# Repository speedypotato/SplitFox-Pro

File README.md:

# SplitFox-Pro
Split-style Pro Leverless Controller

#### This work is licensed under a Creative Commons Attribution-NonCommercial-ShareAlike 4.0 International License.

### Prototype Run For Sale @ https://www.speedylabs.us/product/splitfox-pro-split-fighting-box-pro/ 

## What's the SplitFox Pro?
Speedy Labs introduces the SplitFox Pro - Split Fighting Box (Pro)!  This is a split layout leverless controller with 18 action buttons, 6 aux buttons, and a tournament lockout switch running on GP2040-CE.

### Design
When designing this, I had a few main goals in mind:
1. Split Layout
2. Embeddable PS Auth Dongle (non-protruding)
3. Standard or Mixbox support
4. USB C Daughterboard

Technically this would have been the LightFox Pro, but since I'm using choc v2 here due to the rumored discontinuation of Keychron LP Opticals it would feel wrong to call it that.  Hence SplitFox Pro.  The layout begins with the standard 12 button leverless layout.  I then took the 4 movement buttons and shifted them out one button space, creating the basic split layout.  I then added a button to each side of each thumb, as typical of many 16 button leverless layouts (except these only have one center thumb button, where SplitFox Pro has two).  Similarly, I added an extra button above the punch row as it's very typical to see one here in addition to a left hand pinky button because I believe that all fingers should be able to press a button at a moment's notice.

Some smaller goals, many carried over from the LightFox:
- Maintain acrylic top for artwork
- Aux buttons on both sides of controller for ease of use/preference
- OLED Display
- Mid-frame construction

### BOM
- PCBs
  - 1x SplitFox
  - 1x wasd or wasd-m
  - 1x usb-breakout
  - 1x usb-ext (optional)
- 1x OLED ZJY096-2864KSWEG41X
- Acrylics (2.5mm thickness)
  - 1x splitfox-bottom
  - 1x splitfox-top or splitfox-top-m
- CNC Aluminum (or 3D print if going for a cheaper build)
  - 1x splitfox-body
  - 1x splitfox-wasd-1_2mm or splitfox-wasd-m-1_2mm (both 1.2mm thick)
- 2x EVA Foam Feet splitfox-foot-2mm (or silicone, but it was too expensive for a small run for me)
- 23x m3x6 ultra low profile screws
- 2x m3 nut
- 18x shadow hunting switches (or any choc v2 switch)
- Keycaps
  - 4x 28.5mm
  - 14x 22.5 or 10x 22.5 + WASD (must be low profile mx stem compatible!!)
- Double sided mounting tape (Scotch 314H-MED is a good thickness for the oled in my tests)
- 2x ZH 7 Pin 10cm double headed wire (make sure you don't get the twisted cable version!! correct version e.g. https://ae01.alicdn.com/kf/S88d212727fc34138a45582e0e0a23c315.jpg)
- 3D prints
  - 1x usb-ext-bot
  - 1x usb-ext-top
  - 1x 93657A501_Nylon Unthreaded Spacer

Optionals, but things I would include normally:
- 1x 2mm hex wrench
- 1x 2m usb c cable
- 1x velcro cable tie
- 1x zipper case
- 1x shipping box
- 1x honson F5

### Basic Assembly Instructions
0. Flash SplitFox pcb
1. Plug in OLED and adhere with double sided mounting tape.
2. Plug both ZH cable into SplitFox pcb
3. Screw in SplitFox pcb into splitfox-body
4. Plug WASD ZH cable into wasd pcb
5. Screw wasd pcb into splitfox-body
6. Put splitfox-wasd-1_2mm into topside of splitfox-body, using 93657A501_Nylon Unthreaded Spacer, 1x m3x6, and 1x m3 nut to secure and sandwich together.
7. Insert shadow hunting switches.  Support sockets from backside when inserting to avoid damage.
8. Plug USB ZH cable into usb-breakout pcb
9. Screw in usb-breakout pcb into splitfox-body
10. Apply 2x splitfox-foot-2mm to splitfox-bottom
11. Screw in splitfox-bottom to splitfox-body
12. Add artwork cutout if desired
13. Screw in splitfox-top to splitfox-body

### Video Guides
SplitFox Pro Assembly & Mixbox Setup: https://youtu.be/-rr3WSn5i6s  
SplitFox Pro LED Setup (Beta): https://youtu.be/0wB09UQQ0kg

Done!  Be sure to post your builds on Discord @ https://discord.gg/MmuKd73XbY or Twitter/X and tag me @SpeedyPotato_

### Known Issues
v1.1 SplitFox fixes below issue by changing back to the crystal setup I used to use.  Could also be just a bad batch from v1 as I used a different PCBa for v1.1 too.

With v1, testing has gone fairly smoothly aside from one weird issue, where plugging in an auth dongle causes the controller to freeze/reboot.  If you leave the dongle plugged in all the time, this isn't an issue, but I hope to root cause it someday.  It might be the RP2040 crystal setup or the XC6206 being too weak, but both are also fairly tested in other controllers that don't have issues.  RP2040 crystal setup is new to me but is recommended in RP2040's hardware design guide.  XC6206 is used in production LightFox controllers and those have no issues hotplugging auth devices.

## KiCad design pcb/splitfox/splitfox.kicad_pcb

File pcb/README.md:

# PCB

This is where the PCB source file(s) live

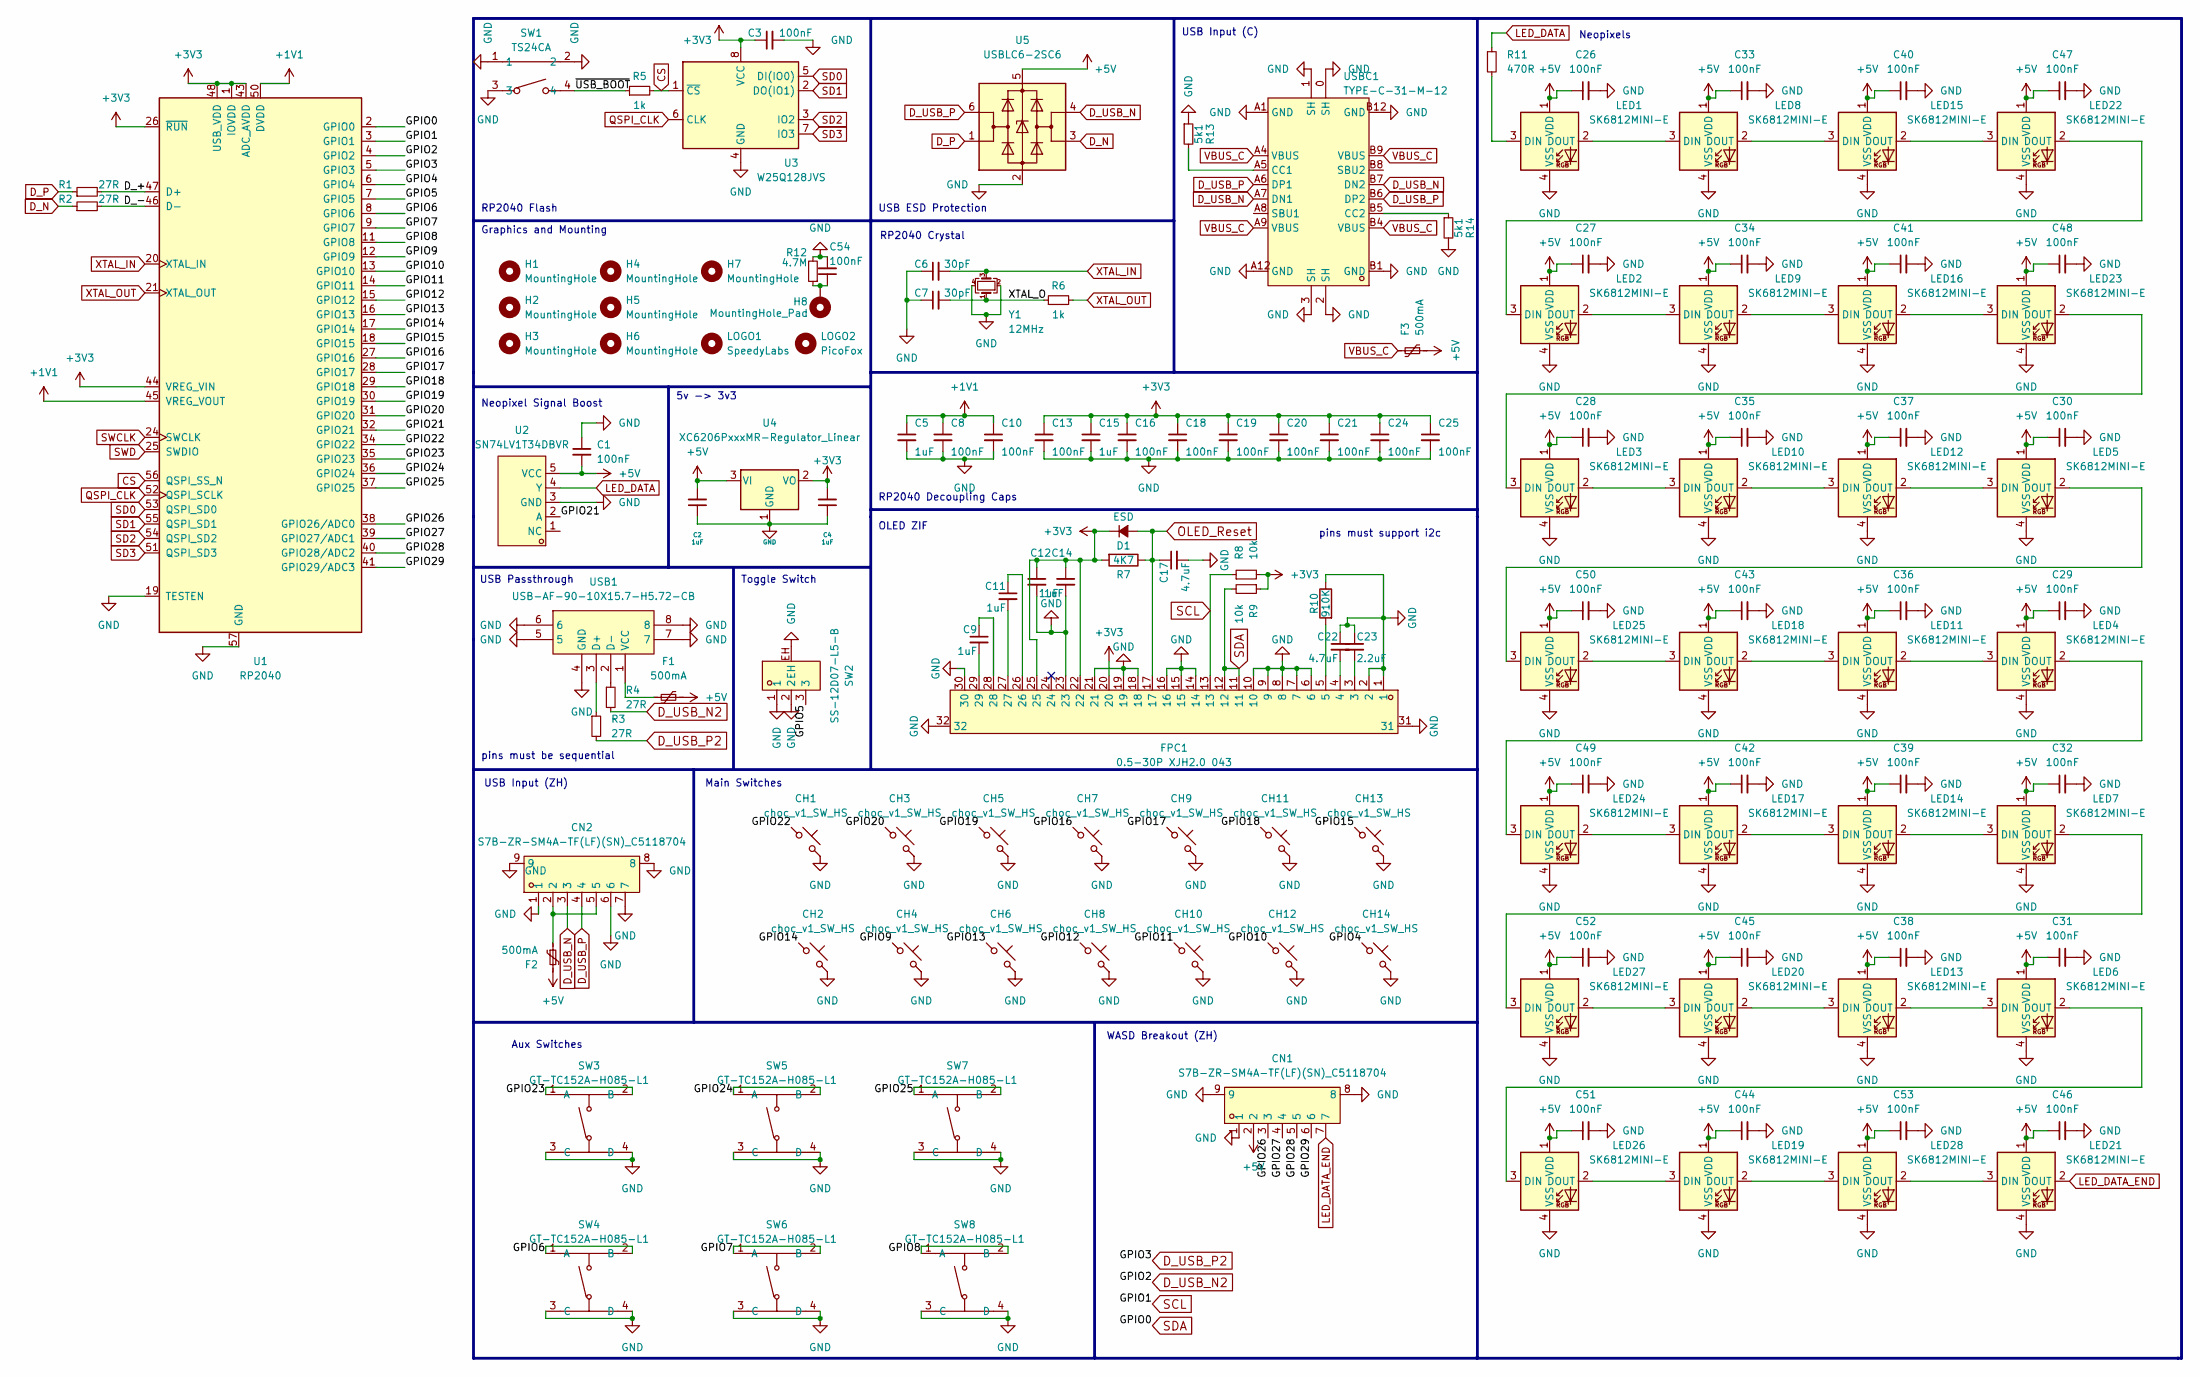
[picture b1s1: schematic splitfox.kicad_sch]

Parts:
C1, C3, C8, C10, C13, C16, C18, C19, C20, C21, C24, C25, C26, C27, C28, C29, C30, C31, C32, C33, C34, C35, C36, C37, C38, C39, C40, C41, C42, C43, C44, C45, C46, C47, C48, C49, C50, C51, C52, C53, C54: 100nF; C_0402_1005Metric; LCSC C1525
C2, C4, C5, C9, C11, C12, C14, C15: 1uF; C_0402_1005Metric; LCSC C52923
C6, C7: 30pF; C_0402_1005Metric; LCSC C1570
C17, C22: 4.7uF; C_0402_1005Metric; LCSC C466620
C23: 2.2uF; C_0402_1005Metric; LCSC C2976056
CH1, CH2, CH3, CH4, CH5, CH6, CH7, CH8, CH9, CH10, CH11, CH12, CH13, CH14: choc_v1_SW_HS; SW_choc_v2_HS_CPG135001S30_1u; LCSC C5333465
CN1, CN2: S7B-ZR-SM4A-TF(LF)(SN)_C5118704; CONN-SMD_S7B-ZR-SM4A-TF-LF-SN; LCSC Part C5118704
D1: ESD; D_SOD-123; LCSC C81598
F1, F2, F3: 500mA; Fuse_1206_3216Metric; LCSC C720075
FPC1: 0.5-30P XJH2.0 043; FPC-SMD_30P-P0.50_0.5-30P-XJH2.0-043; LCSC Part C5373440
H1, H2, H3, H4, H5, H6, H7: MountingHole; MountingHole_3mm
H8: MountingHole_Pad; MountingHole_3mm_Pad
LED1, LED2, LED3, LED4, LED5, LED6, LED7, LED8, LED9, LED10, LED11, LED12, LED13, LED14, LED15, LED16, LED17, LED18, LED19, LED20, LED21, LED22, LED23, LED24, LED25, LED26, LED27, LED28: SK6812MINI-E; LED_6028R; LCSC C5149201
LOGO1: SpeedyLabs; logo
LOGO2: PicoFox; picofox_small
R1, R2, R3, R4: 27R; R_0402_1005Metric; LCSC C137890
R5, R6: 1k; R_0402_1005Metric; LCSC C11702
R7: 4K7; R_0402_1005Metric; LCSC C25900
R8, R9: 10k; R_0402_1005Metric; LCSC C25744
R10: 910K; R_0402_1005Metric; LCSC C25800
R11: 470R; R_0402_1005Metric; LCSC C25117
R12: 4.7M; R_0402_1005Metric; LCSC C474132
R13, R14: 5k1; R_0402_1005Metric; LCSC C25905
SW1: TS24CA; SW-SMD_TS24CA; LCSC Part C393942
SW2: SS-12D07-L5-B; SW-TH_SS-12D07-X-X; LCSC Part C480345
SW3, SW4, SW5, SW6, SW7, SW8: GT-TC152A-H085-L1; SW-TH_4P-L12.0-W12.0-P5.00-LS12.5; LCSC Part C2843937
U1: RP2040; RP2040-QFN-56; LCSC C2040
U2: SN74LV1T34DBVR; SOT-23-5_L2.9-W1.6-P0.95-LS2.8-BR; LCSC Part C100024
U3: W25Q128JVS; SOIC-8_5.23x5.23mm_P1.27mm; LCSC C131025
U4: XC6206PxxxMR-Regulator_Linear; SOT-23; LCSC C5446
U5: USBLC6-2SC6; SOT-23-6; LCSC C2827654
USB1: USB-AF-90-10X15.7-H5.72-CB; USB-A-SMD_C41014; LCSC Part C41014
USBC1: TYPE-C-31-M-12; USB-C_SMD-TYPE-C-31-M-12; LCSC Part C165948
Y1: 12MHz; Crystal_SMD_3225-4Pin_3.2x2.5mm; LCSC C9002

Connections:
+1V1: C5.1, C8.1, C10.1, U1.23 (DVDD), U1.45 (VREG_VOUT), U1.50 (DVDD)
+3V3: C3.1, C4.2, C12.1, C13.1, C14.1, C15.1, C16.1, C18.1, C19.1, C20.1, C21.1, C24.1, C25.1, D1.1 (K), FPC1.20, FPC1.22, FPC1.25, R7.2, R8.2, R9.1, U1.1 (IOVDD), U1.10 (IOVDD), U1.22 (IOVDD), U1.26 (~RUN), U1.33 (IOVDD), U1.42 (IOVDD), U1.43 (ADC_AVDD), U1.44 (VREG_VIN), U1.48 (USB_VDD), U1.49 (IOVDD), U3.8 (VCC), U4.2 (VO)
+5V: C1.2, C2.2, C26.1, C27.1, C28.1, C29.1, C30.1, C31.1, C32.1, C33.1, C34.1, C35.1, C36.1, C37.1, C38.1, C39.1, C40.1, C41.1, C42.1, C43.1, C44.1, C45.1, C46.1, C47.1, C48.1, C49.1, C50.1, C51.1, C52.1, C53.1, CN1.2, F1.1, F2.2, F3.1, LED1.1 (VDD), LED2.1 (VDD), LED3.1 (VDD), LED4.1 (VDD), LED5.1 (VDD), LED6.1 (VDD), LED7.1 (VDD), LED8.1 (VDD), LED9.1 (VDD), LED10.1 (VDD), LED11.1 (VDD), LED12.1 (VDD), LED13.1 (VDD), LED14.1 (VDD), LED15.1 (VDD), LED16.1 (VDD), LED17.1 (VDD), LED18.1 (VDD), LED19.1 (VDD), LED20.1 (VDD), LED21.1 (VDD), LED22.1 (VDD), LED23.1 (VDD), LED24.1 (VDD), LED25.1 (VDD), LED26.1 (VDD), LED27.1 (VDD), LED28.1 (VDD), U2.5 (VCC), U4.3 (VI), U5.5 (VBUS)
/D_+: R1.2, U1.47 (D+)
/D_-: R2.2, U1.46 (D-)
/GPIO4: CH14.1, U1.6 (GPIO4)
/GPIO5: SW2.3, U1.7 (GPIO5)
/GPIO6: SW4.1 (A), SW4.2 (B), U1.8 (GPIO6)
/GPIO7: SW6.1 (A), SW6.2 (B), U1.9 (GPIO7)
/GPIO8: SW8.1 (A), SW8.2 (B), U1.11 (GPIO8)
/GPIO9: CH4.1, U1.12 (GPIO9)
/GPIO10: CH12.1, U1.13 (GPIO10)
/GPIO11: CH10.1, U1.14 (GPIO11)
/GPIO12: CH8.1, U1.15 (GPIO12)
/GPIO13: CH6.1, U1.16 (GPIO13)
/GPIO14: CH2.1, U1.17 (GPIO14)
/GPIO15: CH13.1, U1.18 (GPIO15)
/GPIO16: CH7.1, U1.27 (GPIO16)
/GPIO17: CH9.1, U1.28 (GPIO17)
/GPIO18: CH11.1, U1.29 (GPIO18)
/GPIO19: CH5.1, U1.30 (GPIO19)
/GPIO20: CH3.1, U1.31 (GPIO20)
/GPIO21: U1.32 (GPIO21), U2.2 (A)
/GPIO22: CH1.1, U1.34 (GPIO22)
/GPIO23: SW3.1 (A), SW3.2 (B), U1.35 (GPIO23)
/GPIO24: SW5.1 (A), SW5.2 (B), U1.36 (GPIO24)
/GPIO25: SW7.1 (A), SW7.2 (B), U1.37 (GPIO25)
/GPIO26: CN1.3, U1.38 (GPIO26/ADC0)
/GPIO27: CN1.4, U1.39 (GPIO27/ADC1)
/GPIO28: CN1.5, U1.40 (GPIO28/ADC2)
/GPIO29: CN1.6, U1.41 (GPIO29/ADC3)
/XTAL_O: C7.2, R6.1, Y1.1
/~USB_BOOT: R5.1, SW1.4
CS: R5.2, U1.56 (QSPI_SS_N), U3.1 (~CS)
D_N: R2.1, U5.3 (I/O2)
D_P: R1.1, U5.1 (I/O1)
D_USB_N: CN2.3, U5.4 (I/O2), USBC1.A7 (DN1), USBC1.B7 (DN2)
D_USB_N2: R4.2, U1.4 (GPIO2)
D_USB_P: CN2.4, U5.6 (I/O1), USBC1.A6 (DP1), USBC1.B6 (DP2)
D_USB_P2: R3.2, U1.5 (GPIO3)
GND: C1.1, C2.1, C3.2, C4.1, C5.2, C6.1, C7.1, C8.2, C10.2, C12.2, C13.2, C14.2, C15.2, C16.2, C17.2, C18.2, C19.2, C20.2, C21.2, C22.1, C23.1, C24.2, C25.2, C26.2, C27.2, C28.2, C29.2, C30.2, C31.2, C32.2, C33.2, C34.2, C35.2, C36.2, C37.2, C38.2, C39.2, C40.2, C41.2, C42.2, C43.2, C44.2, C45.2, C46.2, C47.2, C48.2, C49.2, C50.2, C51.2, C52.2, C53.2, C54.2, CH1.2, CH2.2, CH3.2, CH4.2, CH5.2, CH6.2, CH7.2, CH8.2, CH9.2, CH10.2, CH11.2, CH12.2, CH13.2, CH14.2, CN1.1, CN1.8, CN1.9, CN2.1, CN2.6, CN2.7, CN2.8, CN2.9, FPC1.1, FPC1.2, FPC1.6, FPC1.7, FPC1.8, FPC1.9, FPC1.10, FPC1.14, FPC1.15, FPC1.16, FPC1.18, FPC1.19, FPC1.21, FPC1.23, FPC1.30, FPC1.31, FPC1.32, LED1.4 (VSS), LED2.4 (VSS), LED3.4 (VSS), LED4.4 (VSS), LED5.4 (VSS), LED6.4 (VSS), LED7.4 (VSS), LED8.4 (VSS), LED9.4 (VSS), LED10.4 (VSS), LED11.4 (VSS), LED12.4 (VSS), LED13.4 (VSS), LED14.4 (VSS), LED15.4 (VSS), LED16.4 (VSS), LED17.4 (VSS), LED18.4 (VSS), LED19.4 (VSS), LED20.4 (VSS), LED21.4 (VSS), LED22.4 (VSS), LED23.4 (VSS), LED24.4 (VSS), LED25.4 (VSS), LED26.4 (VSS), LED27.4 (VSS), LED28.4 (VSS), R10.1, R12.2, R13.1, R14.2, SW1.1, SW1.2, SW1.3, SW2.1, SW2.2, SW2.EH, SW3.3 (C), SW3.4 (D), SW4.3 (C), SW4.4 (D), SW5.3 (C), SW5.4 (D), SW6.3 (C), SW6.4 (D), SW7.3 (C), SW7.4 (D), SW8.3 (C), SW8.4 (D), U1.19 (TESTEN), U1.57 (GND), U2.3 (GND), U3.4 (GND), U4.1 (GND), U5.2 (GND), USB1.4 (GND), USB1.5, USB1.6, USB1.7, USB1.8, USBC1.0 (SH), USBC1.1 (SH), USBC1.2 (SH), USBC1.3 (SH), USBC1.A1 (GND), USBC1.A12 (GND), USBC1.B1 (GND), USBC1.B12 (GND), Y1.2, Y1.4
LED_DATA: R11.1, U2.4 (Y)
LED_DATA_END: CN1.7, LED21.2 (DOUT)
unnamed: C9.1, FPC1.28
unnamed: C9.2, FPC1.29
unnamed: C11.1, FPC1.26
unnamed: C11.2, FPC1.27
unnamed: C22.2, FPC1.4
unnamed: C23.2, FPC1.3
unnamed: C54.1, H8.1, R12.1
unnamed: CN2.2, CN2.5, F2.1
unnamed: FPC1.5, R10.2
unnamed: LED1.3 (DIN), R11.2
unnamed: LED1.2 (DOUT), LED8.3 (DIN)
unnamed: LED2.3 (DIN), LED22.2 (DOUT)
unnamed: LED2.2 (DOUT), LED9.3 (DIN)
unnamed: LED3.2 (DOUT), LED10.3 (DIN)
unnamed: LED10.2 (DOUT), LED12.3 (DIN)
unnamed: LED11.3 (DIN), LED18.2 (DOUT)
unnamed: LED4.3 (DIN), LED11.2 (DOUT)
unnamed: LED5.3 (DIN), LED12.2 (DOUT)
unnamed: LED13.3 (DIN), LED20.2 (DOUT)
unnamed: LED6.3 (DIN), LED13.2 (DOUT)
unnamed: LED14.3 (DIN), LED17.2 (DOUT)
unnamed: LED7.3 (DIN), LED14.2 (DOUT)
unnamed: LED8.2 (DOUT), LED15.3 (DIN)
unnamed: LED15.2 (DOUT), LED22.3 (DIN)
unnamed: LED9.2 (DOUT), LED16.3 (DIN)
unnamed: LED16.2 (DOUT), LED23.3 (DIN)
unnamed: LED17.3 (DIN), LED24.2 (DOUT)
unnamed: LED18.3 (DIN), LED25.2 (DOUT)
unnamed: LED19.3 (DIN), LED26.2 (DOUT)
unnamed: LED19.2 (DOUT), LED28.3 (DIN)
unnamed: LED20.3 (DIN), LED27.2 (DOUT)
unnamed: LED21.3 (DIN), LED28.2 (DOUT)
unnamed: LED3.3 (DIN), LED23.2 (DOUT)
unnamed: LED4.2 (DOUT), LED24.3 (DIN)
unnamed: LED5.2 (DOUT), LED25.3 (DIN)
unnamed: LED6.2 (DOUT), LED26.3 (DIN)
unnamed: LED7.2 (DOUT), LED27.3 (DIN)
unnamed: R3.1, USB1.3 (D+)
unnamed: R4.1, USB1.2 (D-)
unnamed: F1.2, USB1.1 (VCC)
unnamed: R13.2, USBC1.A5 (CC1)
unnamed: R14.1, USBC1.B5 (CC2)
OLED_Reset: C17.1, D1.2 (A), FPC1.17, R7.1
QSPI_CLK: U1.52 (QSPI_SCLK), U3.6 (CLK)
SCL: FPC1.13, R8.1, U1.3 (GPIO1)
SD0: U1.53 (QSPI_SD0), U3.5 (DI(IO0))
SD1: U1.55 (QSPI_SD1), U3.2 (DO(IO1))
SD2: U1.54 (QSPI_SD2), U3.3 (IO2)
SD3: U1.51 (QSPI_SD3), U3.7 (IO3)
SDA: FPC1.11, FPC1.12, R9.2, U1.2 (GPIO0)
SWCLK: U1.24 (SWCLK)
SWD: U1.25 (SWDIO)
VBUS_C: F3.2, USBC1.A4 (VBUS), USBC1.A9 (VBUS), USBC1.B4 (VBUS), USBC1.B9 (VBUS)
XTAL_IN: C6.2, U1.20 (XTAL_IN), Y1.3
XTAL_OUT: R6.2, U1.21 (XTAL_OUT)

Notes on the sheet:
OLED ZIF
Aux Switches
Neopixel Signal Boost
RP2040 Flash
Toggle Switch
Graphics and Mounting
WASD Breakout (ZH)
USB Passthrough
5v -> 3v3
pins must support i2c
USB Input (ZH)
RP2040 Crystal
USB ESD Protection
pins must be sequential
Neopixels
RP2040 Decoupling Caps
USB Input (C)
Main Switches

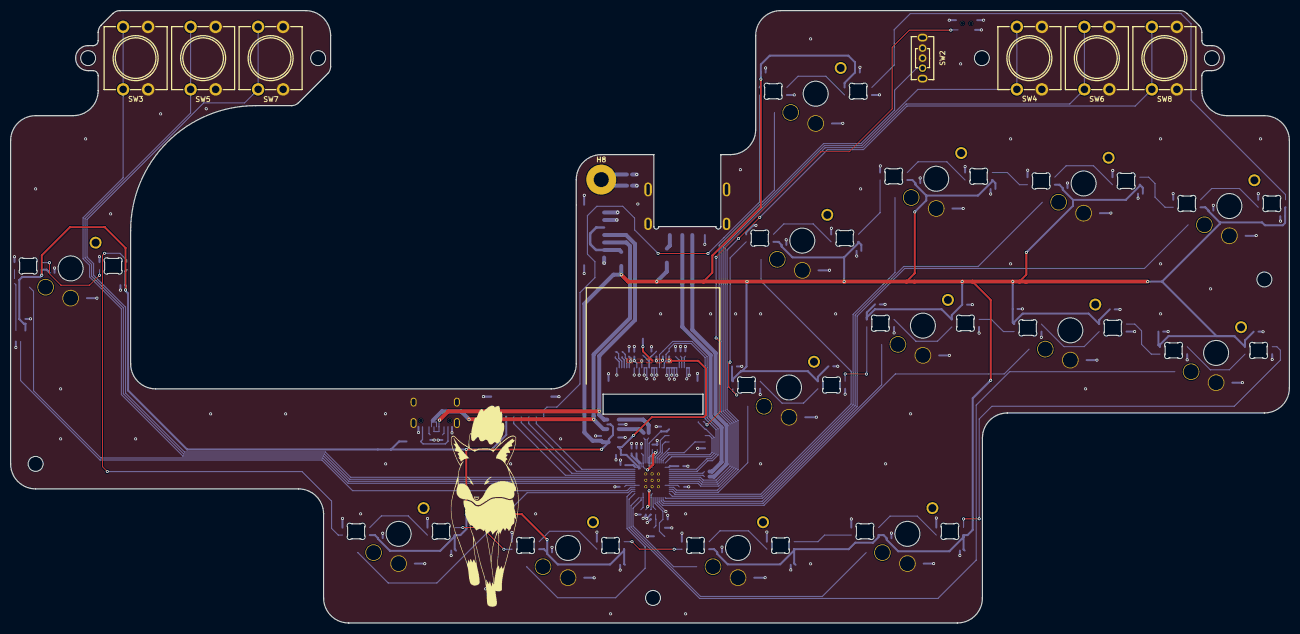
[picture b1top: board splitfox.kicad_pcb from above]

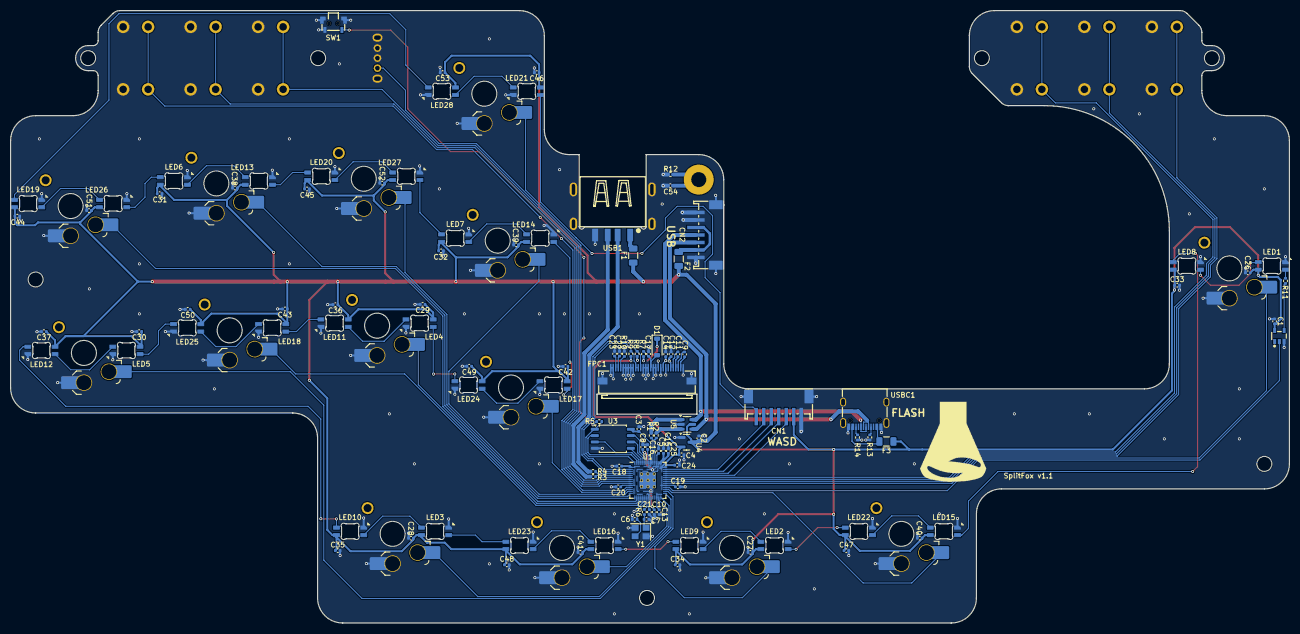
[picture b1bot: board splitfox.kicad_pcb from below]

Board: 2 copper layers, 255.8 x 122.5 mm, 143 parts (127 on the bottom side), 96 nets.

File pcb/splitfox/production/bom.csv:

Designator,Footprint,Quantity,Value,LCSC Part #
"C1, C10, C13, C16, C18, C19, C20, C21, C24, C25, C26, C27, C28, C29, C3, C30, C31, C32, C33, C34, C35, C36, C37, C38, C39, C40, C41, C42, C43, C44, C45, C46, C47, C48, C49, C50, C51, C52, C53, C54, C8",0402,41,100nF,C1525
"C11, C12, C14, C15, C2, C4, C5, C9",0402,8,1uF,C52923
"C17, C22",0402,2,4.7uF,C466620
C23,0402,1,2.2uF,C2976056
"C6, C7",0402,2,30pF,C1570
"CH1, CH10, CH11, CH12, CH13, CH14, CH2, CH3, CH4, CH5, CH6, CH7, CH8, CH9",SW_choc_v2_HS_CPG135001S30_1u,14,choc_v1_SW_HS,C5333465
"CN1, CN2",CONN-SMD_S7B-ZR-SM4A-TF-LF-SN,2,S7B-ZR-SM4A-TF(LF)(SN)_C5118704,C5118704
D1,D_SOD-123,1,ESD,C81598
"F1, F2, F3",1206,3,500mA,C720075
FPC1,FPC-SMD_30P-P0.50_0.5-30P-XJH2.0-043,1,0.5-30P XJH2.0 043,C5373440
"LED1, LED10, LED11, LED12, LED13, LED14, LED15, LED16, LED17, LED18, LED19, LED2, LED20, LED21, LED22, LED23, LED24, LED25, LED26, LED27, LED28, LED3, LED4, LED5, LED6, LED7, LED8, LED9",LED_6028R,28,SK6812MINI-E,C5149201
"R1, R2, R3, R4",0402,4,27R,C137890
R10,0402,1,910K,C25800
R11,0402,1,470R,C25117
R12,0402,1,4.7M,C474132
"R13, R14",0402,2,5k1,C25905
"R5, R6",0402,2,1k,C11702
R7,0402,1,4K7, C25900
"R8, R9",0402,2,10k,C25744
SW1,SW-SMD_TS24CA,1,TS24CA,C393942
SW2,SW-TH_SS-12D07-X-X,1,SS-12D07-L5-B,C480345
"SW3, SW4, SW5, SW6, SW7, SW8",SW-TH_4P-L12.0-W12.0-P5.00-LS12.5,6,GT-TC152A-H085-L1,C2843937
U1,RP2040-QFN-56,1,RP2040,C2040
U2,SOT-23-5_L2.9-W1.6-P0.95-LS2.8-BR,1,SN74LV1T34DBVR,C100024
U3,SOIC-8_5.23x5.23mm_P1.27mm,1,W25Q128JVS,C131025
U4,SOT-23,1,XC6206PxxxMR-Regulator_Linear,C5446
U5,SOT-23-6,1,USBLC6-2SC6,C2827654
USB1,USB-A-SMD_C41014,1,USB-AF-90-10X15.7-H5.72-CB,C41014
USBC1,USB-C_SMD-TYPE-C-31-M-12,1,TYPE-C-31-M-12,C165948
Y1,Crystal_SMD_3225-4Pin_3.2x2.5mm,1,12MHz,C9002

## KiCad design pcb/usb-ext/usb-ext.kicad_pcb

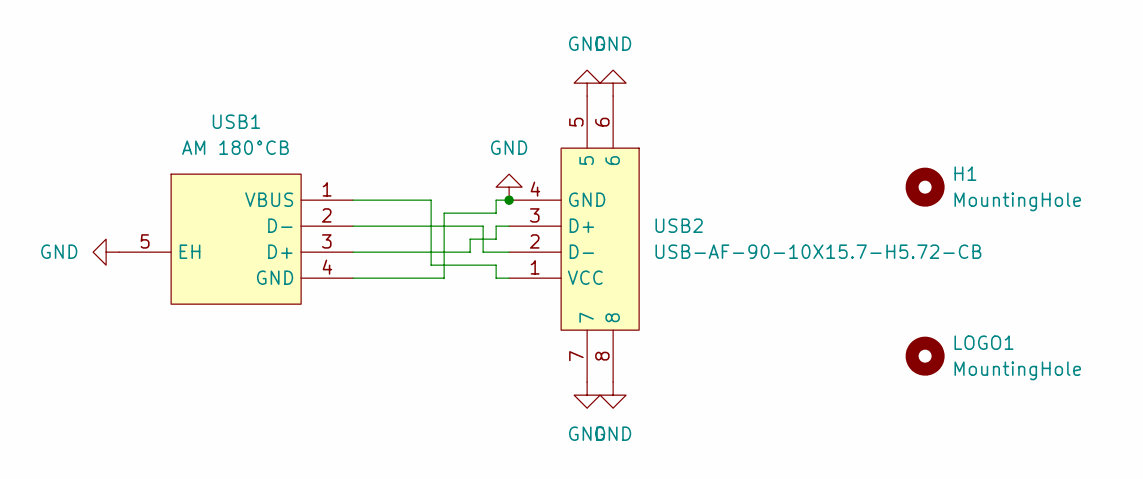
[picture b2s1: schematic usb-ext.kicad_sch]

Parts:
H1: MountingHole; MountingHole_3mm
LOGO1: MountingHole; logo_small
USB1: AM 180°CB; USB-SMD_AM180CB; LCSC Part C2681565
USB2: USB-AF-90-10X15.7-H5.72-CB; USB-A-SMD_C41014; LCSC Part C41014

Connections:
GND: USB1.4 (GND), USB1.5 (EH), USB2.4 (GND), USB2.5, USB2.6, USB2.7, USB2.8
unnamed: USB1.3 (D+), USB2.3 (D+)
unnamed: USB1.2 (D-), USB2.2 (D-)
unnamed: USB1.1 (VBUS), USB2.1 (VCC)

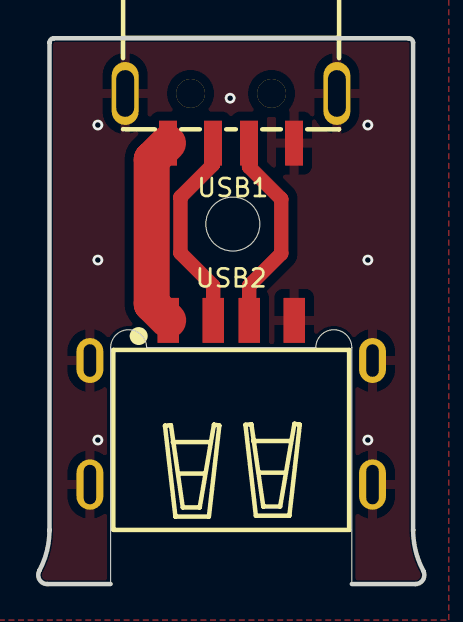
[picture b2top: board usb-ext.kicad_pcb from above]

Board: 2 copper layers, 21.4 x 30.3 mm, 4 parts (1 on the bottom side), 4 nets.

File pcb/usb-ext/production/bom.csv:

Designator,Footprint,Quantity,Value,LCSC Part #
USB1,USB-SMD_AM180CB,1,AM 180°CB,C2681565
USB2,USB-A-SMD_C41014,1,USB-AF-90-10X15.7-H5.72-CB,C41014

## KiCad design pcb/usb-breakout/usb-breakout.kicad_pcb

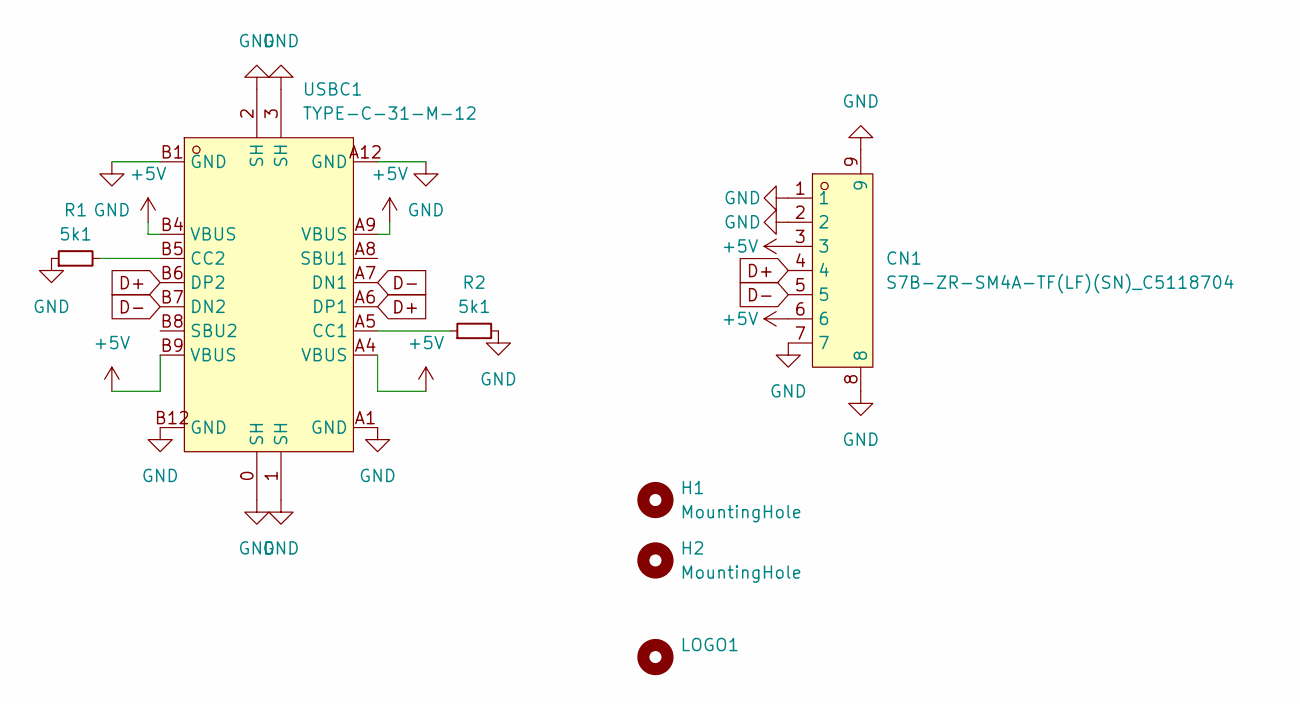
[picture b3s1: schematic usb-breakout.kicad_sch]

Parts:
CN1: S7B-ZR-SM4A-TF(LF)(SN)_C5118704; CONN-SMD_S7B-ZR-SM4A-TF-LF-SN; LCSC Part C5118704
H1, H2: MountingHole; MountingHole_3mm
LOGO1: MountingHole; logo_small
R1, R2: 5k1; R_0402_1005Metric_Pad0.72x0.64mm_HandSolder; LCSC C25905
USBC1: TYPE-C-31-M-12; USB-C_SMD-TYPE-C-31-M-12; LCSC Part C165948

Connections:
+5V: CN1.3, CN1.6, USBC1.A4 (VBUS), USBC1.A9 (VBUS), USBC1.B4 (VBUS), USBC1.B9 (VBUS)
D+: CN1.4, USBC1.A6 (DP1), USBC1.B6 (DP2)
D-: CN1.5, USBC1.A7 (DN1), USBC1.B7 (DN2)
GND: CN1.1, CN1.2, CN1.7, CN1.8, CN1.9, R1.1, R2.2, USBC1.0 (SH), USBC1.1 (SH), USBC1.2 (SH), USBC1.3 (SH), USBC1.A1 (GND), USBC1.A12 (GND), USBC1.B1 (GND), USBC1.B12 (GND)
unnamed: R2.1, USBC1.A5 (CC1)
unnamed: R1.2, USBC1.B5 (CC2)

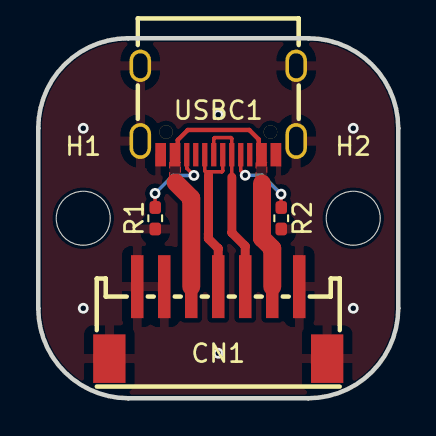
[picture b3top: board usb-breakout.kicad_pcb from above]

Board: 2 copper layers, 20.0 x 20.0 mm, 7 parts (1 on the bottom side), 6 nets.

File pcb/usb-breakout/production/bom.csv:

Designator,Footprint,Quantity,Value,LCSC Part #
CN1,CONN-SMD_S7B-ZR-SM4A-TF-LF-SN,1,S7B-ZR-SM4A-TF(LF)(SN)_C5118704,C5118704
"R1, R2",0402,2,5k1,C25905
USBC1,USB-C_SMD-TYPE-C-31-M-12,1,TYPE-C-31-M-12,C165948

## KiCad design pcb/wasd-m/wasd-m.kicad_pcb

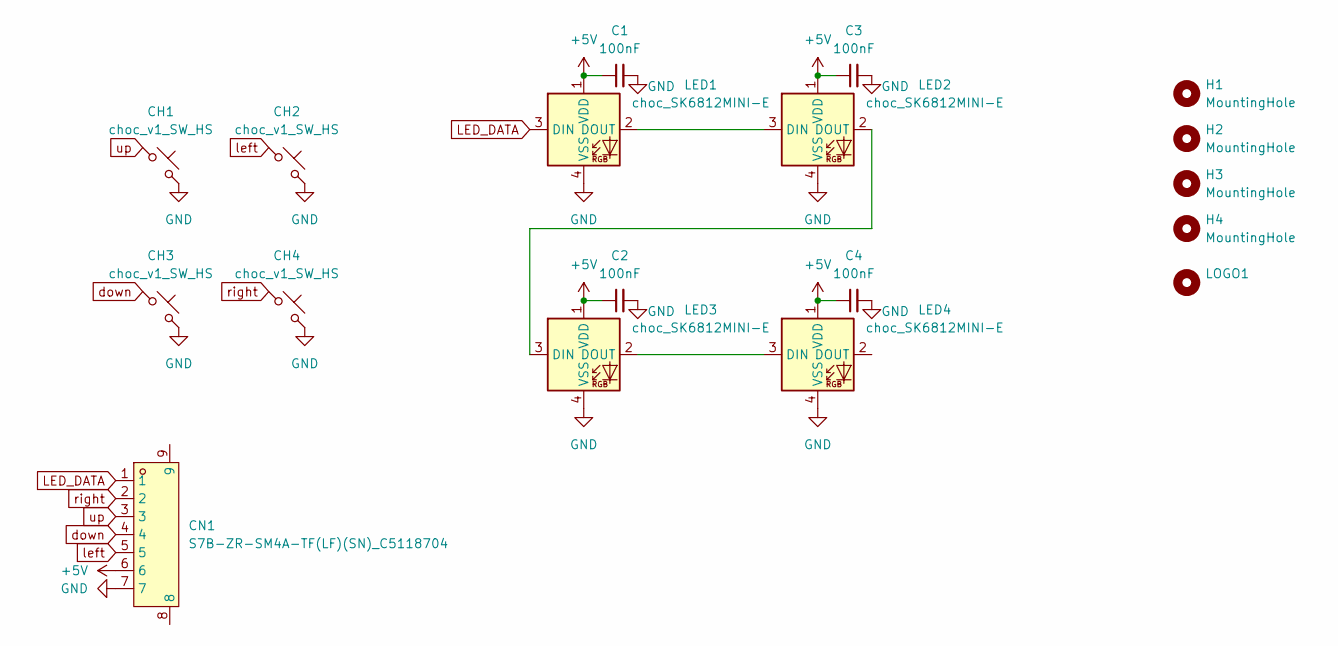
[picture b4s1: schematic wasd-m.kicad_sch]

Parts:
C1, C2, C3, C4: 100nF; C_0402_1005Metric; LCSC C1525
CH1, CH2, CH3, CH4: choc_v1_SW_HS; SW_choc_v2_HS_CPG135001S30_1u; LCSC C5333465
CN1: S7B-ZR-SM4A-TF(LF)(SN)_C5118704; CONN-SMD_S7B-ZR-SM4A-TF-LF-SN; LCSC Part C5118704
H1, H2, H3, H4: MountingHole; MountingHole_3mm
LED1, LED2, LED3, LED4: choc_SK6812MINI-E; LED_choc_6028R; LCSC C5149201
LOGO1: MountingHole; logo_small

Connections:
+5V: C1.1, C2.1, C3.1, C4.1, CN1.6, LED1.1 (VDD), LED2.1 (VDD), LED3.1 (VDD), LED4.1 (VDD)
GND: C1.2, C2.2, C3.2, C4.2, CH1.2, CH2.2, CH3.2, CH4.2, CN1.7, LED1.4 (VSS), LED2.4 (VSS), LED3.4 (VSS), LED4.4 (VSS)
LED_DATA: CN1.1, LED1.3 (DIN)
unnamed: LED1.2 (DOUT), LED2.3 (DIN)
unnamed: LED2.2 (DOUT), LED3.3 (DIN)
unnamed: LED3.2 (DOUT), LED4.3 (DIN)
down: CH3.1, CN1.4
left: CH2.1, CN1.5
right: CH4.1, CN1.2
up: CH1.1, CN1.3

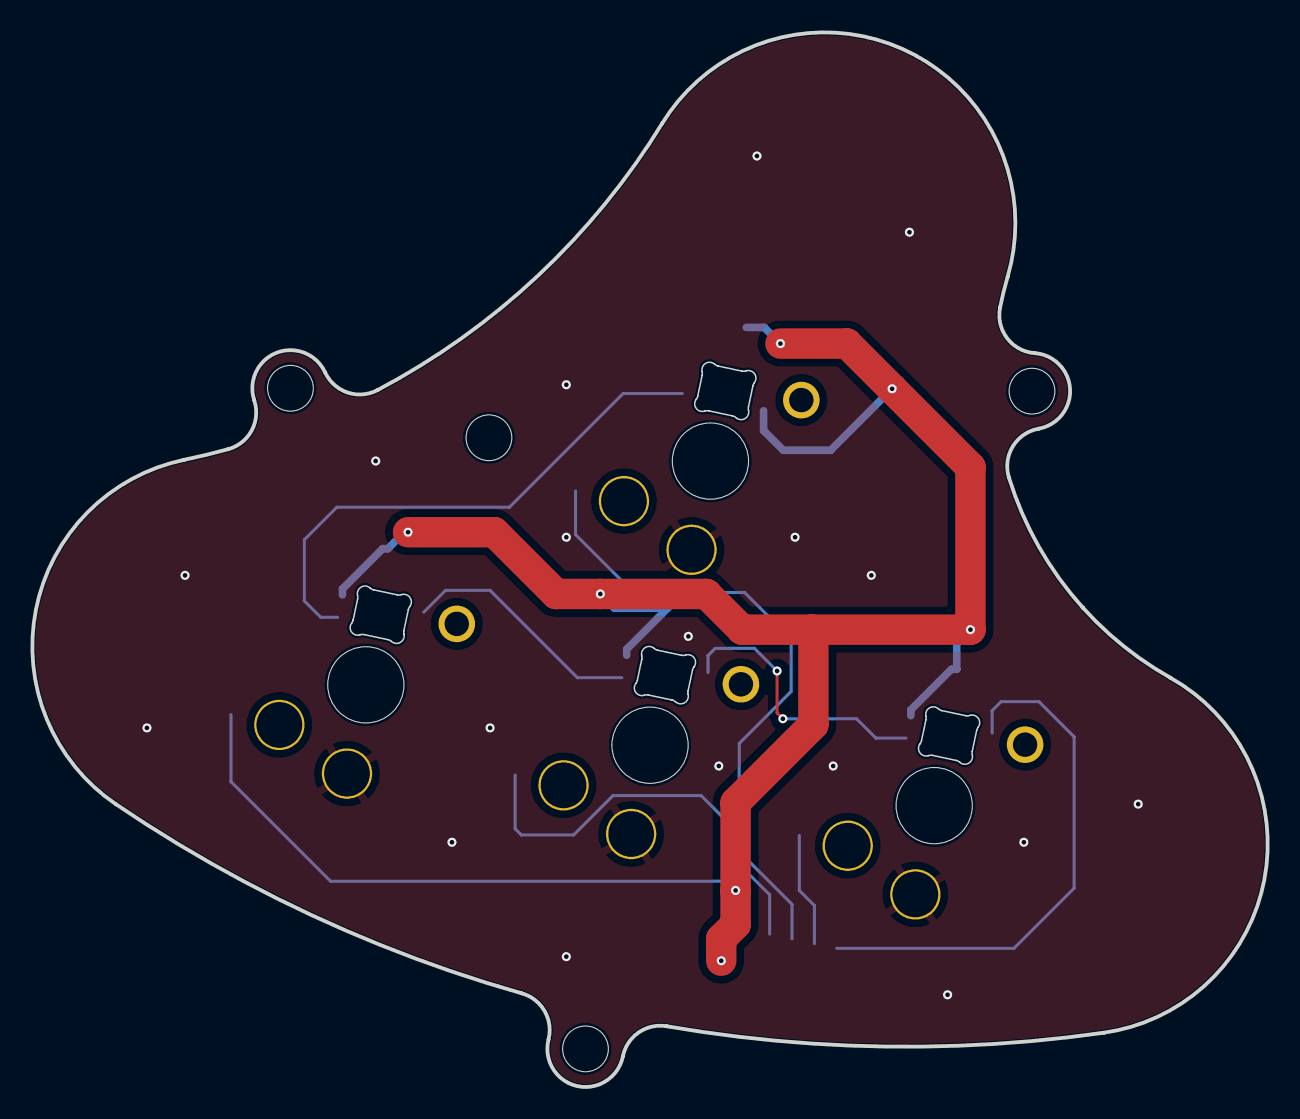
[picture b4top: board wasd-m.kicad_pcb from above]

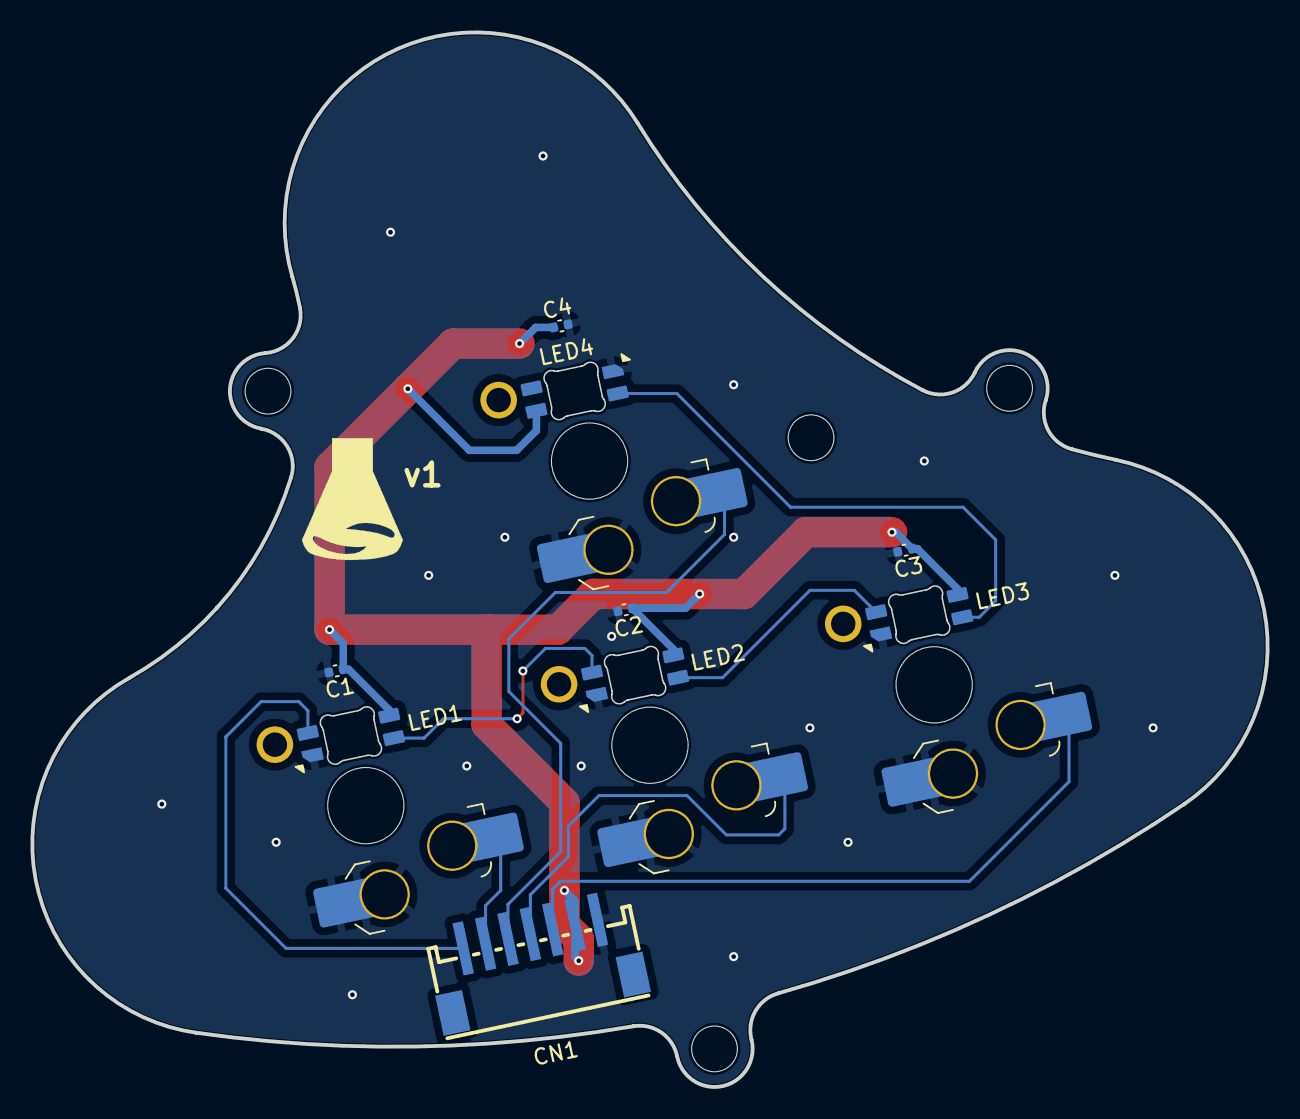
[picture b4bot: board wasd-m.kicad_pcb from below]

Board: 2 copper layers, 81.0 x 69.2 mm, 18 parts (18 on the bottom side), 10 nets.

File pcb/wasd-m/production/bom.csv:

Designator,Footprint,Quantity,Value,LCSC Part #
"C1, C2, C3, C4",0402,4,100nF,C1525
"CH1, CH2, CH3, CH4",SW_choc_v2_HS_CPG135001S30_1u,4,choc_v1_SW_HS,C5333465
CN1,CONN-SMD_S7B-ZR-SM4A-TF-LF-SN,1,S7B-ZR-SM4A-TF(LF)(SN)_C5118704,C5118704
"LED1, LED2, LED3, LED4",LED_choc_6028R,4,choc_SK6812MINI-E,C5149201

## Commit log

2025-01-18 NG | WIP Base Cad
2025-01-20 NG | RGB and wasd tweaks
2025-01-22 NG | PCB shape
2025-01-30 NG | Honson F5 cad, updated splitfox-base, consider going bottom single load after today
2025-02-02 NG | Move to bottom assembly + through hole tops
2025-02-02 NG | Enclosure finished
2025-02-03 NG | USB Boards
2025-02-03 NG | WASD wip, led issue
2025-02-03 NG | Updated layouts with leds, todo: pcb layout
2025-02-03 NG | wasd pcb
2025-02-04 NG | Update usb ext pinout, cleanup
2025-02-04 NG | Cad assembly updated, ready for main pcb
2025-02-10 NG | SplitFox Schematic
2025-02-11 NG | Splitfox PCB Placement
2025-02-12 NG | DRC Cleanup
2025-02-12 NG | Ready for routing
2025-02-12 NG | SplitFox PCB, Redid body cad
2025-02-12 NG | Fixed assembly, dongle should go in 2.5667mm more and usb_ext needs to be adjusted
2025-02-12 NG | It's done-ish, pcb tweaks, assembly
2025-02-13 NG | ESD/EMI caps, USB C flash port
2025-02-13 NG | Assembly fixed, MIX assembly
2025-02-13 NG | Body Print Test
2025-02-14 NG | mix plate test
2025-02-15 NG | 2.5mm acrylics, art dxf
2025-02-15 NG | Test acrylic laser exports
2025-03-01 NG | Test foot print
2025-03-10 NG | CAD Exports
2025-03-11 NG | USB-EXT housing
2025-03-11 NG | usb ext fixes, exports
2025-03-11 NG | Further fixes to usb-ext housing
2025-03-12 NG | 2.5mm plate test
2025-03-13 NG | Added spacer for wasd
2025-03-14 NG | Update README.md, add license before going public
2025-03-15 NG | Added foot alignment tool
2025-03-15 NG | Added holes for foot tool when flipped
2025-03-16 NG | Test firmware updates
2025-03-17 NG | v1.1 SplitFox PCB - old crystal setup test
2025-03-18 NG | Foot Tool curve fixes
2025-03-22 NG | Legal art template for testing
2025-04-08 NG | Test web ui rgb led firmware
2025-04-10 NG | Updated test firmware
2025-04-20 NG | Updated firmware, pictures
2025-07-08 NG | 0.7.11 beta firmware
2025-07-13 NG | 0.7.11 beta firmware 2, fixes touchy usb host
2025-08-09 NG | 0.7.11 beta 3 with usb auth updates
